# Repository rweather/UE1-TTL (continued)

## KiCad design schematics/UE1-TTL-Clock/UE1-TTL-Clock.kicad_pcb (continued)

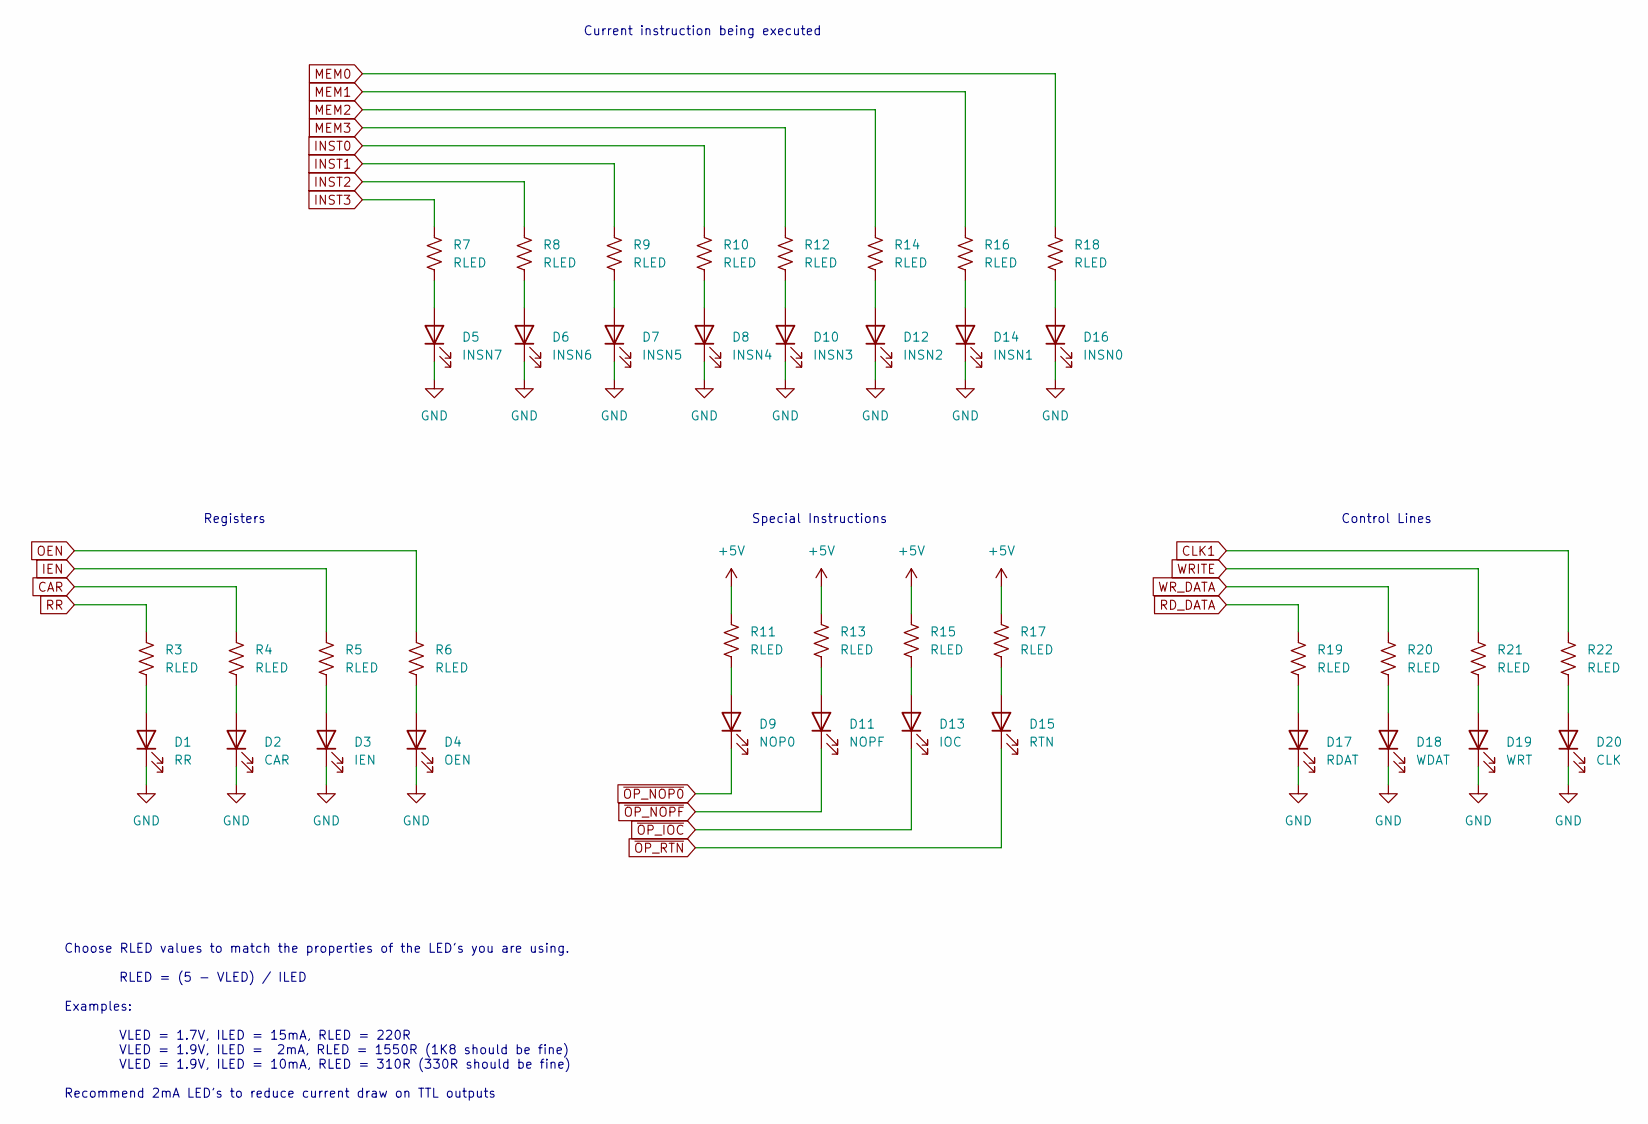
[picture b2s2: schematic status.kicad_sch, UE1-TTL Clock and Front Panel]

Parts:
D1: RR; LED_D3.0mm
D2: CAR; LED_D3.0mm
D3: IEN; LED_D3.0mm
D4: OEN; LED_D3.0mm
D5: INSN7; LED_D3.0mm
D6: INSN6; LED_D3.0mm
D7: INSN5; LED_D3.0mm
D8: INSN4; LED_D3.0mm
D9: NOP0; LED_D3.0mm
D10: INSN3; LED_D3.0mm
D11: NOPF; LED_D3.0mm
D12: INSN2; LED_D3.0mm
D13: IOC; LED_D3.0mm
D14: INSN1; LED_D3.0mm
D15: RTN; LED_D3.0mm
D16: INSN0; LED_D3.0mm
D17: RDAT; LED_D3.0mm
D18: WDAT; LED_D3.0mm
D19: WRT; LED_D3.0mm
D20: CLK; LED_D3.0mm
R3, R4, R5, R6, R7, R8, R9, R10, R11, R12, R13, R14, R15, R16, R17, R18, R19, R20, R21, R22: RLED; R_Axial_DIN0207_L6.3mm_D2.5mm_P7.62mm_Horizontal

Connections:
+5V: R11.1, R13.1, R15.1, R17.1; also elsewhere on the board
CAR: R4.1; also elsewhere on the board
CLK1: R22.1; also elsewhere on the board
GND: D1.1 (K), D2.1 (K), D3.1 (K), D4.1 (K), D5.1 (K), D6.1 (K), D7.1 (K), D8.1 (K), D10.1 (K), D12.1 (K), D14.1 (K), D16.1 (K), D17.1 (K), D18.1 (K), D19.1 (K), D20.1 (K); also elsewhere on the board
IEN: R5.1; also elsewhere on the board
INST0: R10.1; also elsewhere on the board
INST1: R9.1; also elsewhere on the board
INST2: R8.1; also elsewhere on the board
INST3: R7.1; also elsewhere on the board
MEM0: R18.1; also elsewhere on the board
MEM1: R16.1; also elsewhere on the board
MEM2: R14.1; also elsewhere on the board
MEM3: R12.1; also elsewhere on the board
unnamed: D1.2 (A), R3.2
unnamed: D2.2 (A), R4.2
unnamed: D3.2 (A), R5.2
unnamed: D4.2 (A), R6.2
unnamed: D5.2 (A), R7.2
unnamed: D6.2 (A), R8.2
unnamed: D7.2 (A), R9.2
unnamed: D8.2 (A), R10.2
unnamed: D9.2 (A), R11.2
unnamed: D10.2 (A), R12.2
unnamed: D11.2 (A), R13.2
unnamed: D12.2 (A), R14.2
unnamed: D13.2 (A), R15.2
unnamed: D14.2 (A), R16.2
unnamed: D15.2 (A), R17.2
unnamed: D16.2 (A), R18.2
unnamed: D17.2 (A), R19.2
unnamed: D18.2 (A), R20.2
unnamed: D19.2 (A), R21.2
unnamed: D20.2 (A), R22.2
OEN: R6.1; also elsewhere on the board
RD_DATA: R19.1; also elsewhere on the board
RR: R3.1; also elsewhere on the board
WRITE: R21.1; also elsewhere on the board
WR_DATA: R20.1; also elsewhere on the board
~OP_IOC: D13.1 (K); also elsewhere on the board
~OP_NOP0: D9.1 (K); also elsewhere on the board
~OP_NOPF: D11.1 (K); also elsewhere on the board
~OP_RTN: D15.1 (K); also elsewhere on the board

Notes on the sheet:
Choose RLED values to match the properties of the LED's you are using. RLED = (5 - VLED) / ILED Examples: VLED = 1.7V, ILED = 15mA, RLED = 220R VLED = 1.9V, ILED = 2mA, RLED = 1550R (1K8 should be fine) VLED = 1.9V, ILED = 10mA, RLED = 310R (330R should be fine) Recommend 2mA LED's to reduce curren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
Registers
Special Instructions
Control Lines
Current instruction being executed

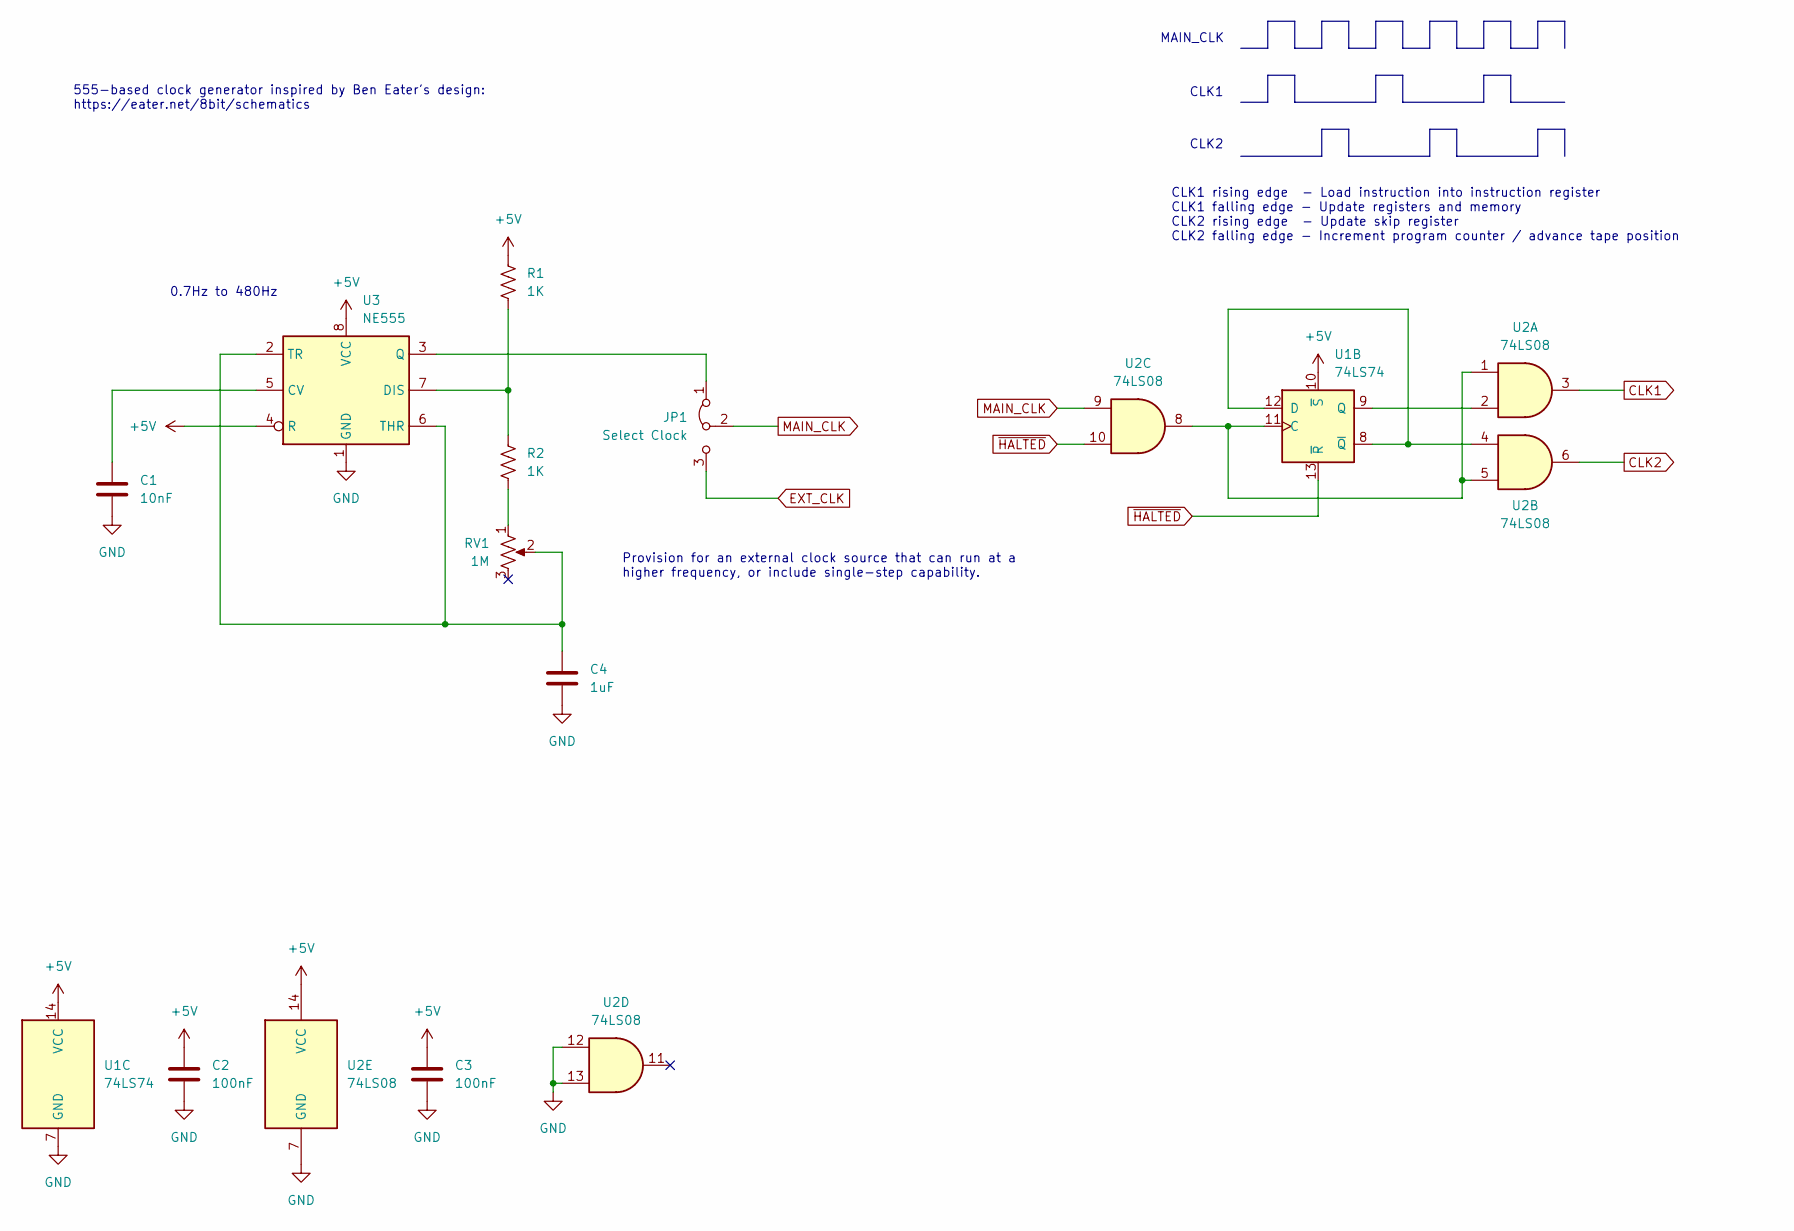
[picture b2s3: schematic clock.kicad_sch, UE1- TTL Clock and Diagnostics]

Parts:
C1: 10nF; C_Disc_D5.0mm_W2.5mm_P5.00mm
C2, C3: 100nF; C_Disc_D5.0mm_W2.5mm_P5.00mm
C4: 1uF; C_Disc_D5.0mm_W2.5mm_P5.00mm
JP1: Select Clock; PinHeader_1x03_P2.54mm_Vertical
R1, R2: 1K; R_Axial_DIN0207_L6.3mm_D2.5mm_P7.62mm_Horizontal
RV1: 1M; Potentiometer_Bourns_3266Y_Vertical
U1: 74LS74; DIP-14_W7.62mm
U2: 74LS08; DIP-14_W7.62mm
U3: NE555; DIP-8_W7.62mm

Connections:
+5V: C2.1, C3.1, R1.1, U1.10 (~S), U1.14 (VCC), U2.14 (VCC), U3.4 (R), U3.8 (VCC); also elsewhere on the board
CLK1: U2.3; also elsewhere on the board
CLK2: U2.6; also elsewhere on the board
EXT_CLK: JP1.3 (B); also elsewhere on the board
GND: C1.2, C2.2, C3.2, C4.2, U1.7 (GND), U2.7 (GND), U2.12, U2.13, U3.1 (GND); also elsewhere on the board
MAIN_CLK: JP1.2 (C), U2.9
unnamed 53: JP1.1 (A), U3.3 (Q); also elsewhere on the board
unnamed: R2.2, RV1.1
unnamed: U1.11 (C), U2.1, U2.5, U2.8
unnamed: U1.8 (~Q), U1.12 (D), U2.4
unnamed: U1.9 (Q), U2.2
unnamed: C1.1, U3.5 (CV)
unnamed: R1.2, R2.1, U3.7 (DIS)
unnamed: C4.1, RV1.2, U3.2 (TR), U3.6 (THR)
~HALTED: U1.13 (~R), U2.10; also elsewhere on the board

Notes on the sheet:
0.7Hz to 480Hz
Provision for an external clock source that can run at a higher frequency, or include single-step capability.
CLK1 rising edge - Load instruction into instruction register CLK1 falling edge - Update registers and memory CLK2 rising edge - Update skip register CLK2 falling edge - Increment program counter / advance tape position
555-based clock generator inspired by Ben Eater's design: https://eater.net/8bit/schematics
MAIN_CLK
CLK2
CLK1

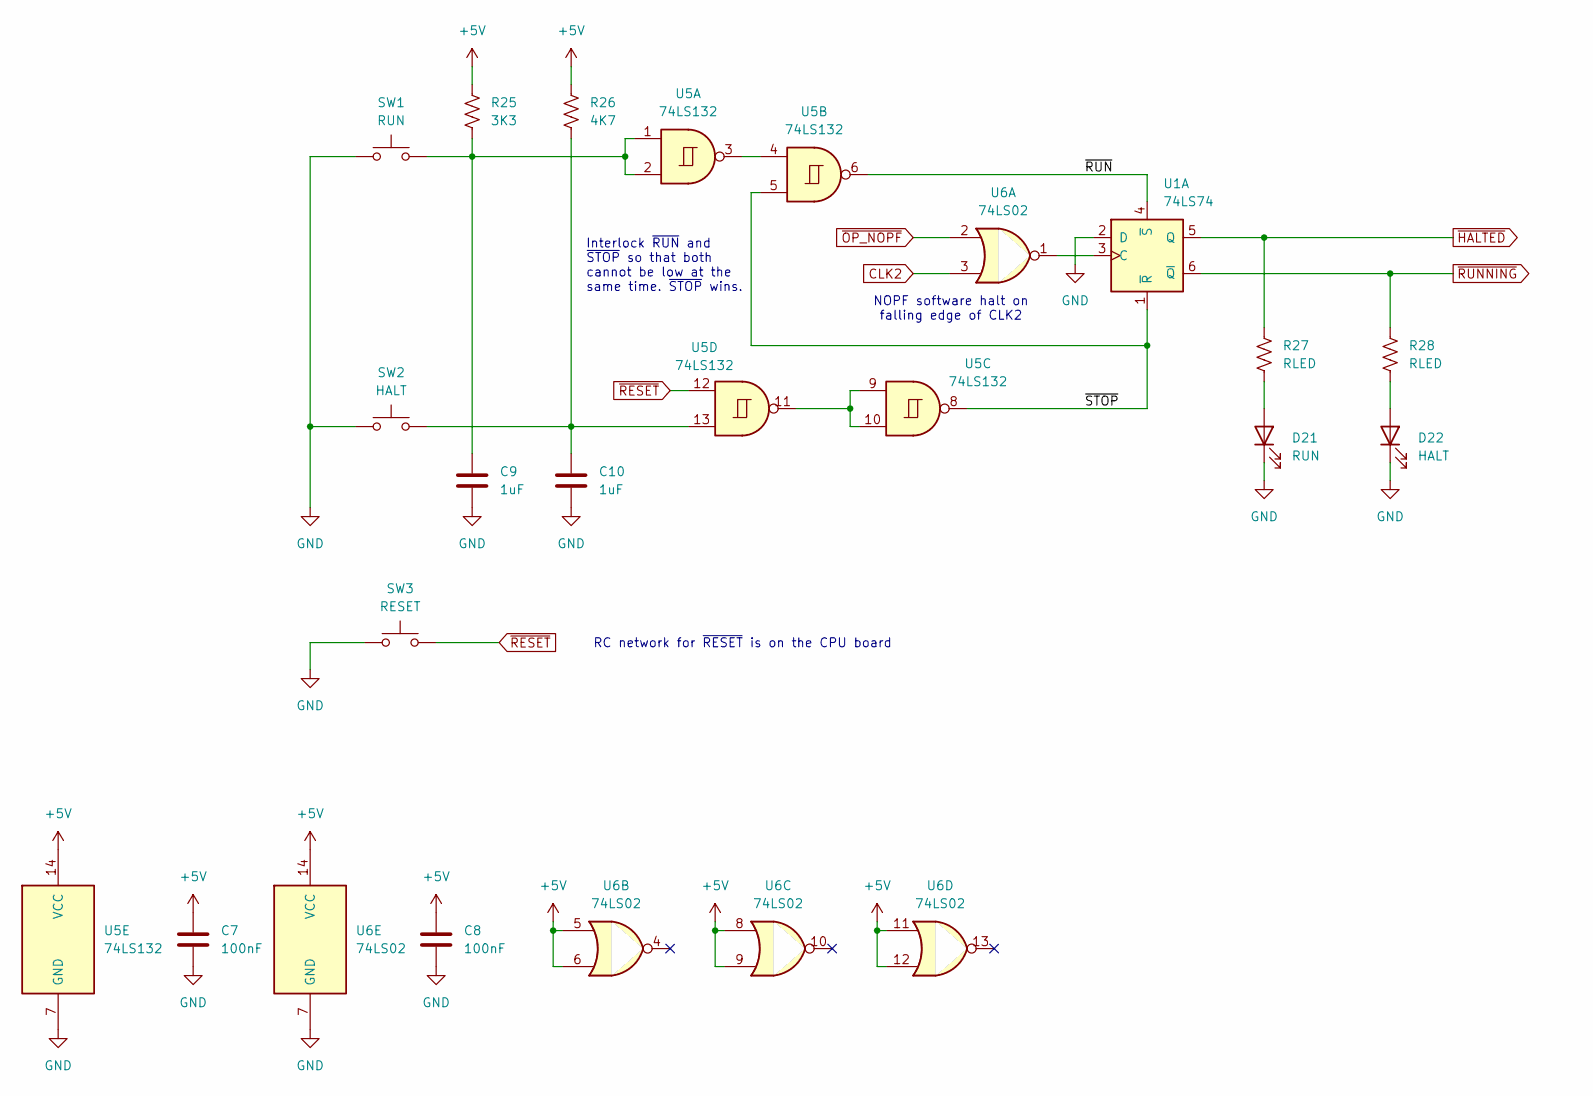
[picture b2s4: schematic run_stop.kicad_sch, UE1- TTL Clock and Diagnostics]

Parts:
C7, C8: 100nF; C_Disc_D5.0mm_W2.5mm_P5.00mm
C9, C10: 1uF; C_Disc_D5.0mm_W2.5mm_P5.00mm
D21: RUN; LED_D3.0mm
D22: HALT; LED_D3.0mm
R25: 3K3; R_Axial_DIN0207_L6.3mm_D2.5mm_P7.62mm_Horizontal
R26: 4K7; R_Axial_DIN0207_L6.3mm_D2.5mm_P7.62mm_Horizontal
R27, R28: RLED; R_Axial_DIN0207_L6.3mm_D2.5mm_P7.62mm_Horizontal
SW1: RUN; SW_PUSH_6mm
SW2: HALT; SW_PUSH_6mm
SW3: RESET; SW_PUSH_6mm
U1: 74LS74; DIP-14_W7.62mm
U5: 74LS132; DIP-14_W7.62mm
U6: 74LS02; DIP-14_W7.62mm

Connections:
+5V: C7.1, C8.1, R25.1, R26.1, U5.14 (VCC), U6.5, U6.6, U6.8, U6.9, U6.11, U6.12, U6.14 (VCC); also elsewhere on the board
/Run Stop/~RUN: U1.4 (~S), U5.6
/Run Stop/~STOP: U1.1 (~R), U5.5, U5.8
CLK2: U6.3; also elsewhere on the board
GND: C7.2, C8.2, C9.2, C10.2, D21.1 (K), D22.1 (K), SW1.1, SW2.1, SW3.1, U1.2 (D), U5.7 (GND), U6.7 (GND); also elsewhere on the board
unnamed: C9.1, R25.2, SW1.2, U5.1, U5.2
unnamed: C10.1, R26.2, SW2.2, U5.13
unnamed: D21.2 (A), R27.2
unnamed: D22.2 (A), R28.2
unnamed: U1.3 (C), U6.1
unnamed: U5.3, U5.4
unnamed: U5.9, U5.10, U5.11
~HALTED: R27.1, U1.5 (Q); also elsewhere on the board
~OP_NOPF: U6.2; also elsewhere on the board
~RESET: SW3.2, U5.12; also elsewhere on the board
~RUNNING: R28.1, U1.6 (~Q)

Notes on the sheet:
RC network for ~{RESET} is on the CPU board
NOPF software halt on falling edge of CLK2
Interlock ~{RUN} and ~{STOP} so that both cannot be low at the same time. ~{STOP} wins.

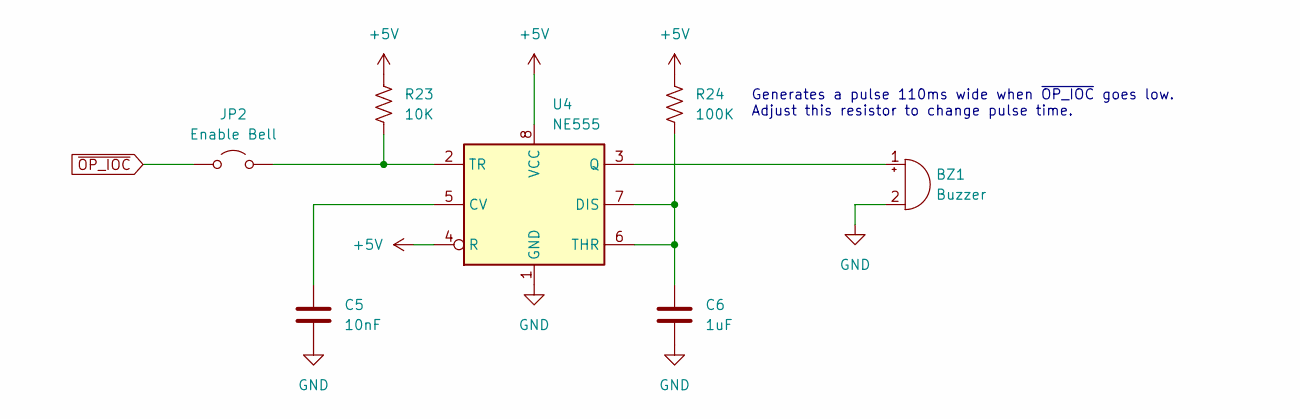
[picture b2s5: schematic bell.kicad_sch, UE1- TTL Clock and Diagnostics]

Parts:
BZ1: Buzzer; Buzzer_12x9.5RM7.6
C5: 10nF; C_Disc_D5.0mm_W2.5mm_P5.00mm
C6: 1uF; C_Disc_D5.0mm_W2.5mm_P5.00mm
JP2: Enable Bell; PinHeader_1x02_P2.54mm_Vertical
R23: 10K; R_Axial_DIN0207_L6.3mm_D2.5mm_P7.62mm_Horizontal
R24: 100K; R_Axial_DIN0207_L6.3mm_D2.5mm_P7.62mm_Horizontal
U4: NE555; DIP-8_W7.62mm

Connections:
+5V: R23.1, R24.1, U4.4 (R), U4.8 (VCC); also elsewhere on the board
GND: BZ1.2 (-), C5.2, C6.2, U4.1 (GND); also elsewhere on the board
unnamed: BZ1.1 (+), U4.3 (Q)
unnamed: JP2.2 (B), R23.2, U4.2 (TR)
unnamed: C5.1, U4.5 (CV)
unnamed: C6.1, R24.2, U4.6 (THR), U4.7 (DIS)
~OP_IOC: JP2.1 (A); also elsewhere on the board

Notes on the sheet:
Generates a pulse 110ms wide when ~{OP_IOC} goes low. Adjust this resistor to change pulse time.

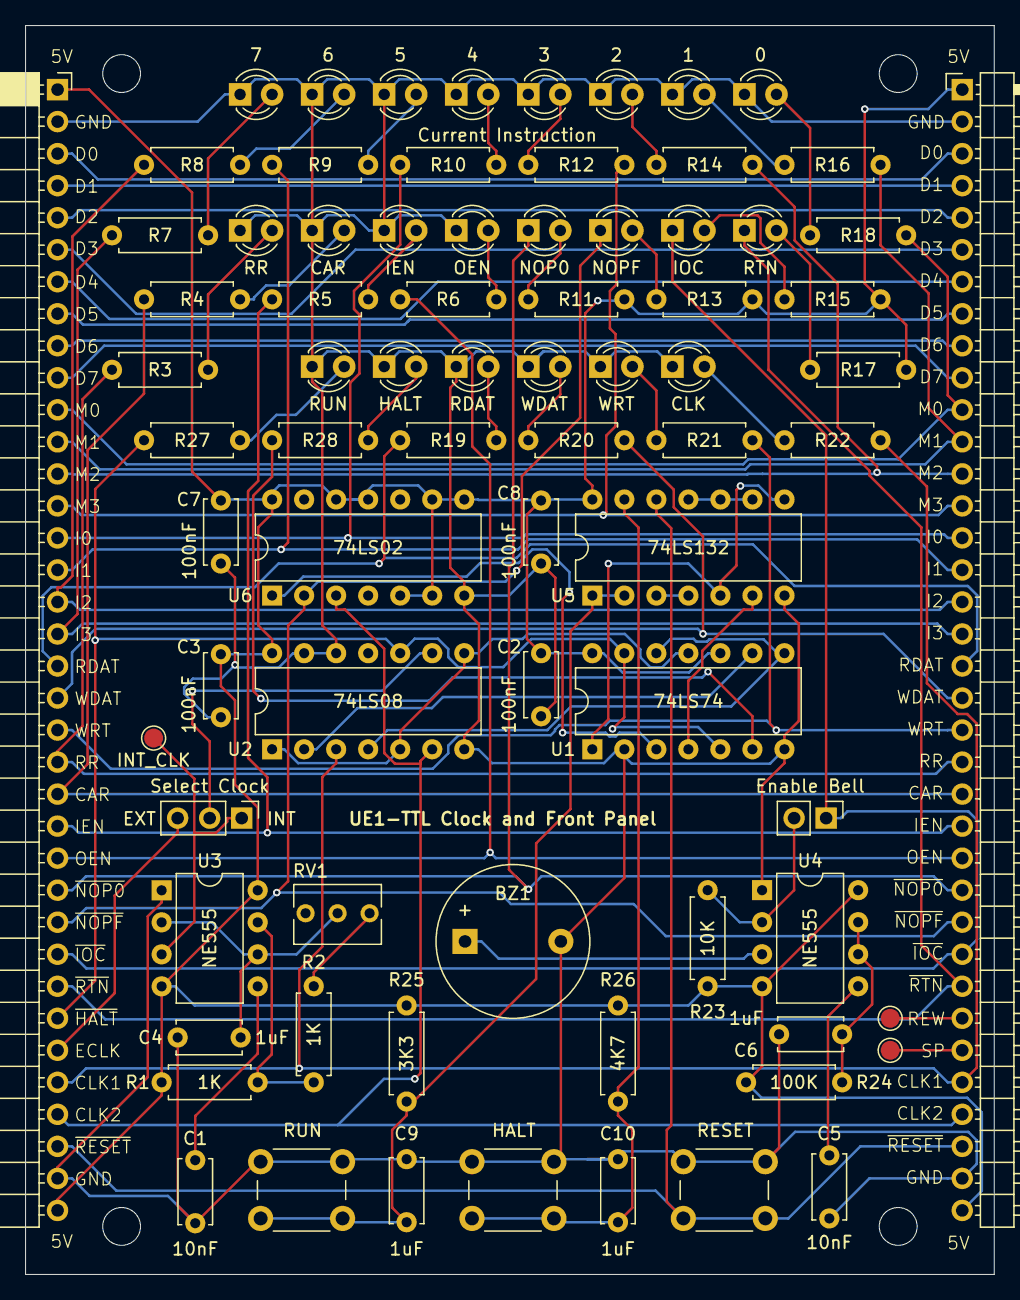
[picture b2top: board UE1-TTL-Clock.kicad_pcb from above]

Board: 2 copper layers, 76.8 x 99.1 mm, 82 parts (0 on the bottom side), 79 nets.

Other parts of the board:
TP1: REWIND; TestPoint_Pad_D1.5mm
TP2: SPARE; TestPoint_Pad_D1.5mm
TP3: INT_CLK; TestPoint_Pad_D1.5mm

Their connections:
unnamed 51: TP1.1; also elsewhere on the board
unnamed 52: TP2.1; also elsewhere on the board
unnamed 53: TP3.1; also elsewhere on the board

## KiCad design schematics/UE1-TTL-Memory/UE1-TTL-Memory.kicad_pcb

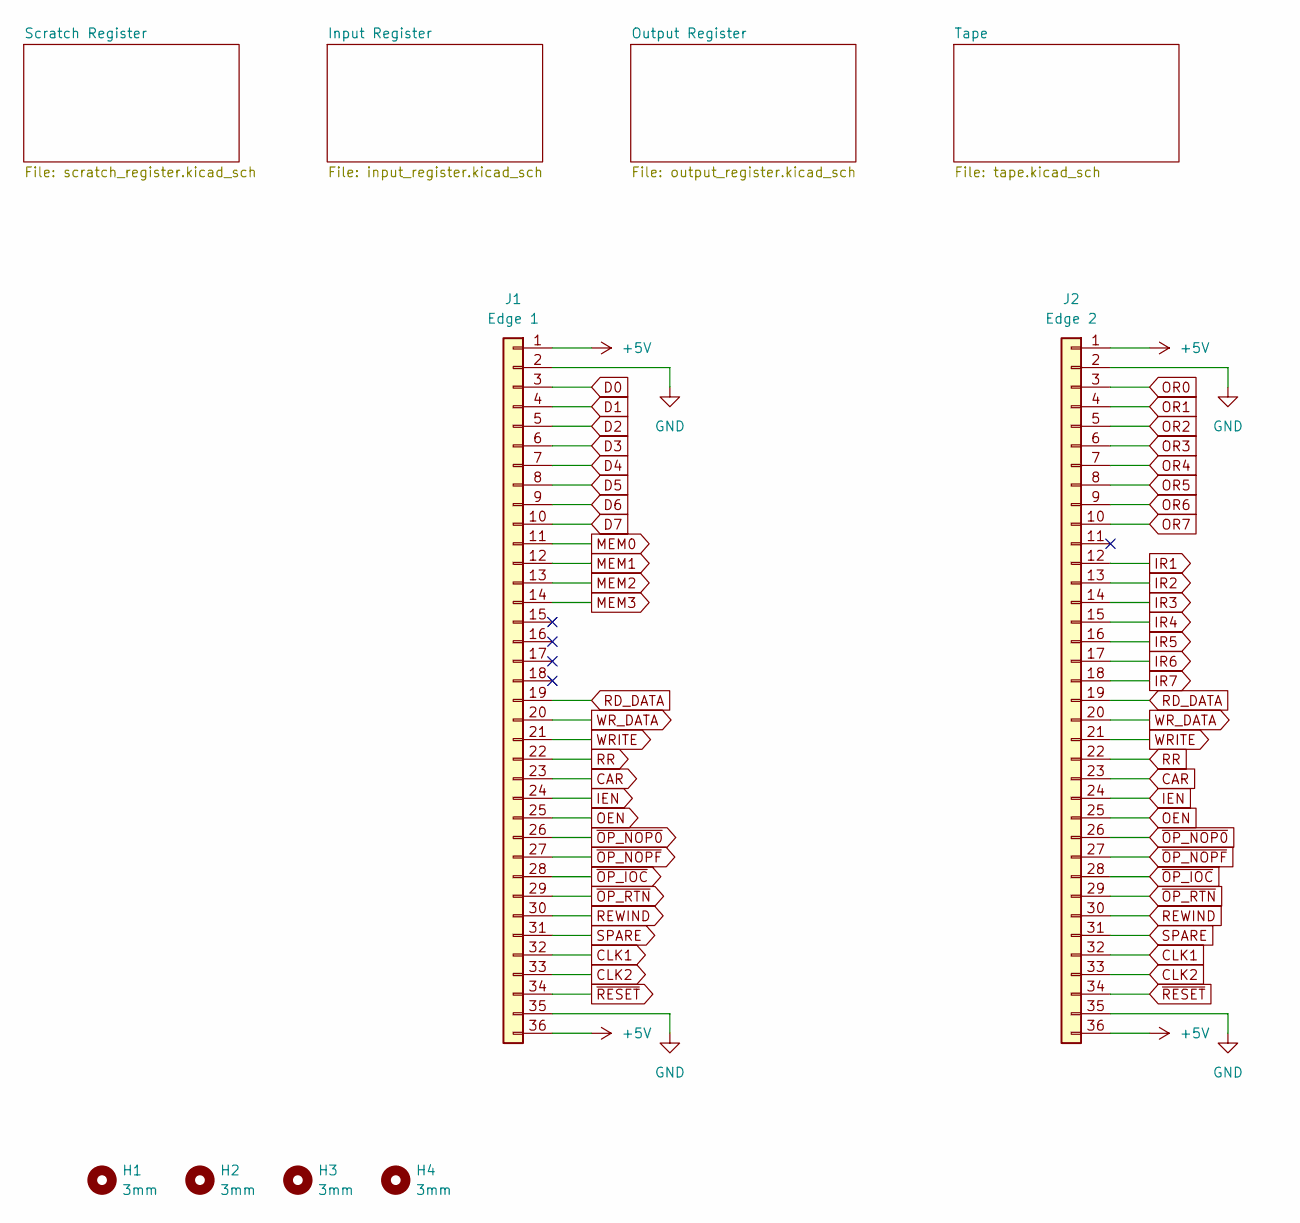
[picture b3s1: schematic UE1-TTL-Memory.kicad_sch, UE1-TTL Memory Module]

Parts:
H1, H2, H3, H4: 3mm; MountingHole_3mm
J1: Edge 1; PinSocket_1x36_P2.54mm_Horizontal
J2: Edge 2; PinHeader_1x36_P2.54mm_Horizontal

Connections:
+5V: J1.1, J1.36, J2.1, J2.36; also elsewhere on the board
CAR: J1.23, J2.23
CLK1: J1.32, J2.32
CLK2: J1.33, J2.33; also elsewhere on the board
D0: J1.3; also elsewhere on the board
D1: J1.4; also elsewhere on the board
D2: J1.5; also elsewhere on the board
D3: J1.6; also elsewhere on the board
D4: J1.7; also elsewhere on the board
D5: J1.8; also elsewhere on the board
D6: J1.9; also elsewhere on the board
D7: J1.10; also elsewhere on the board
GND: J1.2, J1.35, J2.2, J2.35; also elsewhere on the board
IEN: J1.24, J2.24
IR1: J2.12; also elsewhere on the board
IR2: J2.13; also elsewhere on the board
IR3: J2.14; also elsewhere on the board
IR4: J2.15; also elsewhere on the board
IR5: J2.16; also elsewhere on the board
IR6: J2.17; also elsewhere on the board
IR7: J2.18; also elsewhere on the board
MEM0: J1.11; also elsewhere on the board
MEM1: J1.12; also elsewhere on the board
MEM2: J1.13; also elsewhere on the board
MEM3: J1.14; also elsewhere on the board
OEN: J1.25, J2.25
OR0: J2.3; also elsewhere on the board
OR1: J2.4; also elsewhere on the board
OR2: J2.5; also elsewhere on the board
OR3: J2.6; also elsewhere on the board
OR4: J2.7; also elsewhere on the board
OR5: J2.8; also elsewhere on the board
OR6: J2.9; also elsewhere on the board
OR7: J2.10; also elsewhere on the board
RD_DATA: J1.19, J2.19; also elsewhere on the board
REWIND: J1.30, J2.30; also elsewhere on the board
RR: J1.22, J2.22; also elsewhere on the board
SPARE: J1.31, J2.31
WRITE: J1.21, J2.21; also elsewhere on the board
WR_DATA: J1.20, J2.20; also elsewhere on the board
~OP_IOC: J1.28, J2.28
~OP_NOP0: J1.26, J2.26
~OP_NOPF: J1.27, J2.27
~OP_RTN: J1.29, J2.29
~RESET: J1.34, J2.34; also elsewhere on the board

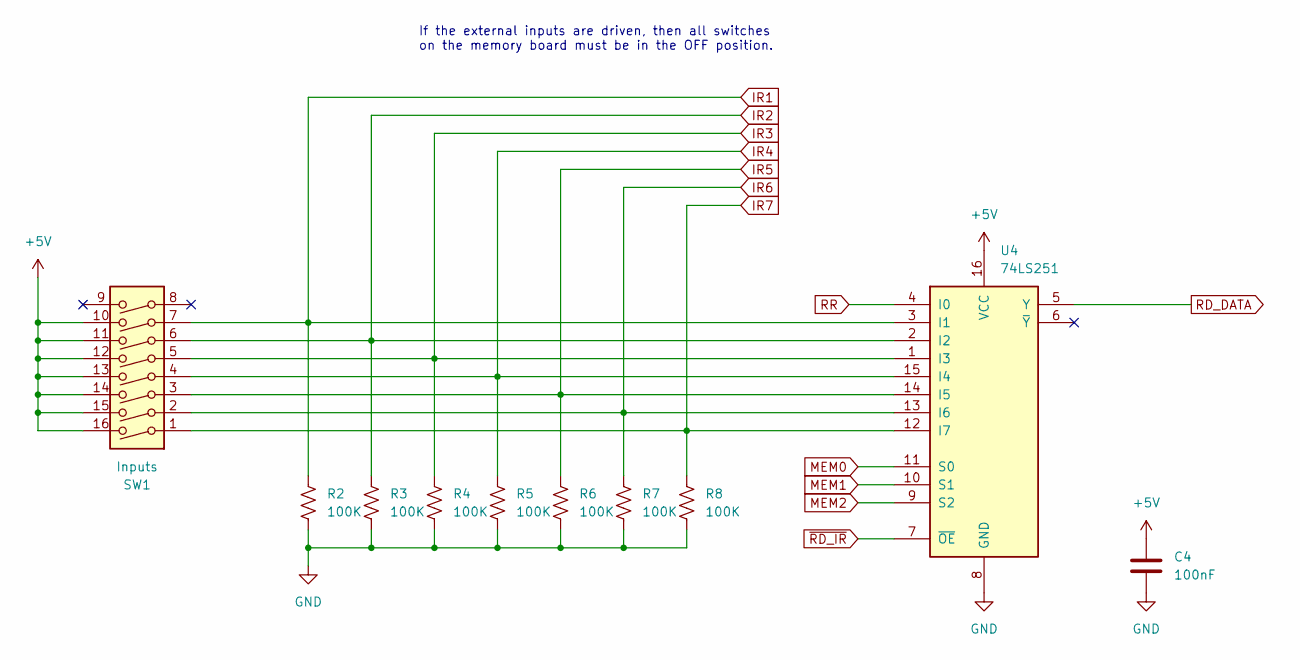
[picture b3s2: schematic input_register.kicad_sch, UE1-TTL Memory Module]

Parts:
C4: 100nF; C_Disc_D5.0mm_W2.5mm_P5.00mm
R2, R3, R4, R5, R6, R7, R8: 100K; R_Axial_DIN0207_L6.3mm_D2.5mm_P7.62mm_Horizontal
SW1: Inputs; SW_DIP_SPSTx08_Slide_6.7x21.88mm_W7.62mm_P2.54mm_LowProfile
U4: 74LS251; DIP-16_W7.62mm

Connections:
+5V: C4.1, SW1.10, SW1.11, SW1.12, SW1.13, SW1.14, SW1.15, SW1.16, U4.16 (VCC); also elsewhere on the board
GND: C4.2, R2.2, R3.2, R4.2, R5.2, R6.2, R7.2, R8.2, U4.8 (GND); also elsewhere on the board
IR1: R2.1, SW1.7, U4.3 (I1); also elsewhere on the board
IR2: R3.1, SW1.6, U4.2 (I2); also elsewhere on the board
IR3: R4.1, SW1.5, U4.1 (I3); also elsewhere on the board
IR4: R5.1, SW1.4, U4.15 (I4); also elsewhere on the board
IR5: R6.1, SW1.3, U4.14 (I5); also elsewhere on the board
IR6: R7.1, SW1.2, U4.13 (I6); also elsewhere on the board
IR7: R8.1, SW1.1, U4.12 (I7); also elsewhere on the board
MEM0: U4.11 (S0); also elsewhere on the board
MEM1: U4.10 (S1); also elsewhere on the board
MEM2: U4.9 (S2); also elsewhere on the board
RD_DATA: U4.5 (Y); also elsewhere on the board
RR: U4.4 (I0); also elsewhere on the board
~RD_IR: U4.7 (~OE); also elsewhere on the board

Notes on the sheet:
If the external inputs are driven, then all switches on the memory board must be in the OFF position.

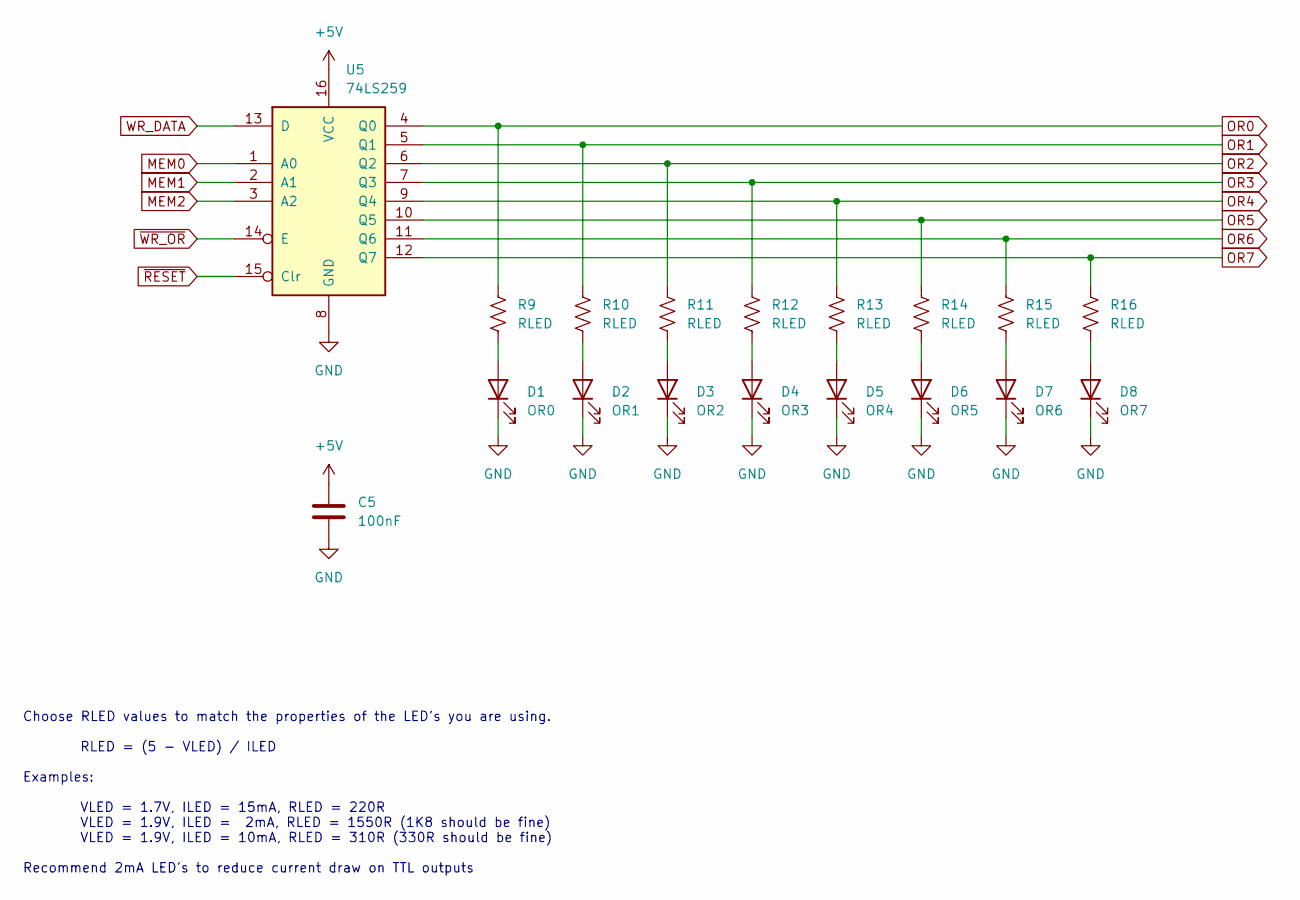
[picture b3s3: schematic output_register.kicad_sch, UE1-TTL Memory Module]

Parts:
C5: 100nF; C_Disc_D5.0mm_W2.5mm_P5.00mm
D1: OR0; LED_D3.0mm
D2: OR1; LED_D3.0mm
D3: OR2; LED_D3.0mm
D4: OR3; LED_D3.0mm
D5: OR4; LED_D3.0mm
D6: OR5; LED_D3.0mm
D7: OR6; LED_D3.0mm
D8: OR7; LED_D3.0mm
R9, R10, R11, R12, R13, R14, R15, R16: RLED; R_Axial_DIN0207_L6.3mm_D2.5mm_P7.62mm_Horizontal
U5: 74LS259; DIP-16_W7.62mm

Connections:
+5V: C5.1, U5.16 (VCC); also elsewhere on the board
GND: C5.2, D1.1 (K), D2.1 (K), D3.1 (K), D4.1 (K), D5.1 (K), D6.1 (K), D7.1 (K), D8.1 (K), U5.8 (GND); also elsewhere on the board
MEM0: U5.1 (A0); also elsewhere on the board
MEM1: U5.2 (A1); also elsewhere on the board
MEM2: U5.3 (A2); also elsewhere on the board
unnamed: D1.2 (A), R9.2
unnamed: D2.2 (A), R10.2
unnamed: D3.2 (A), R11.2
unnamed: D4.2 (A), R12.2
unnamed: D5.2 (A), R13.2
unnamed: D6.2 (A), R14.2
unnamed: D7.2 (A), R15.2
unnamed: D8.2 (A), R16.2
OR0: R9.1, U5.4 (Q0); also elsewhere on the board
OR1: R10.1, U5.5 (Q1); also elsewhere on the board
OR2: R11.1, U5.6 (Q2); also elsewhere on the board
OR3: R12.1, U5.7 (Q3); also elsewhere on the board
OR4: R13.1, U5.9 (Q4); also elsewhere on the board
OR5: R14.1, U5.10 (Q5); also elsewhere on the board
OR6: R15.1, U5.11 (Q6); also elsewhere on the board
OR7: R16.1, U5.12 (Q7); also elsewhere on the board
WR_DATA: U5.13 (D); also elsewhere on the board
~RESET: U5.15 (Clr); also elsewhere on the board
~WR_OR: U5.14 (E); also elsewhere on the board

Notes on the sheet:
Choose RLED values to match the properties of the LED's you are using. RLED = (5 - VLED) / ILED Examples: VLED = 1.7V, ILED = 15mA, RLED = 220R VLED = 1.9V, ILED = 2mA, RLED = 1550R (1K8 should be fine) VLED = 1.9V, ILED = 10mA, RLED = 310R (330R should be fine) Recommend 2mA LED's to reduce curren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

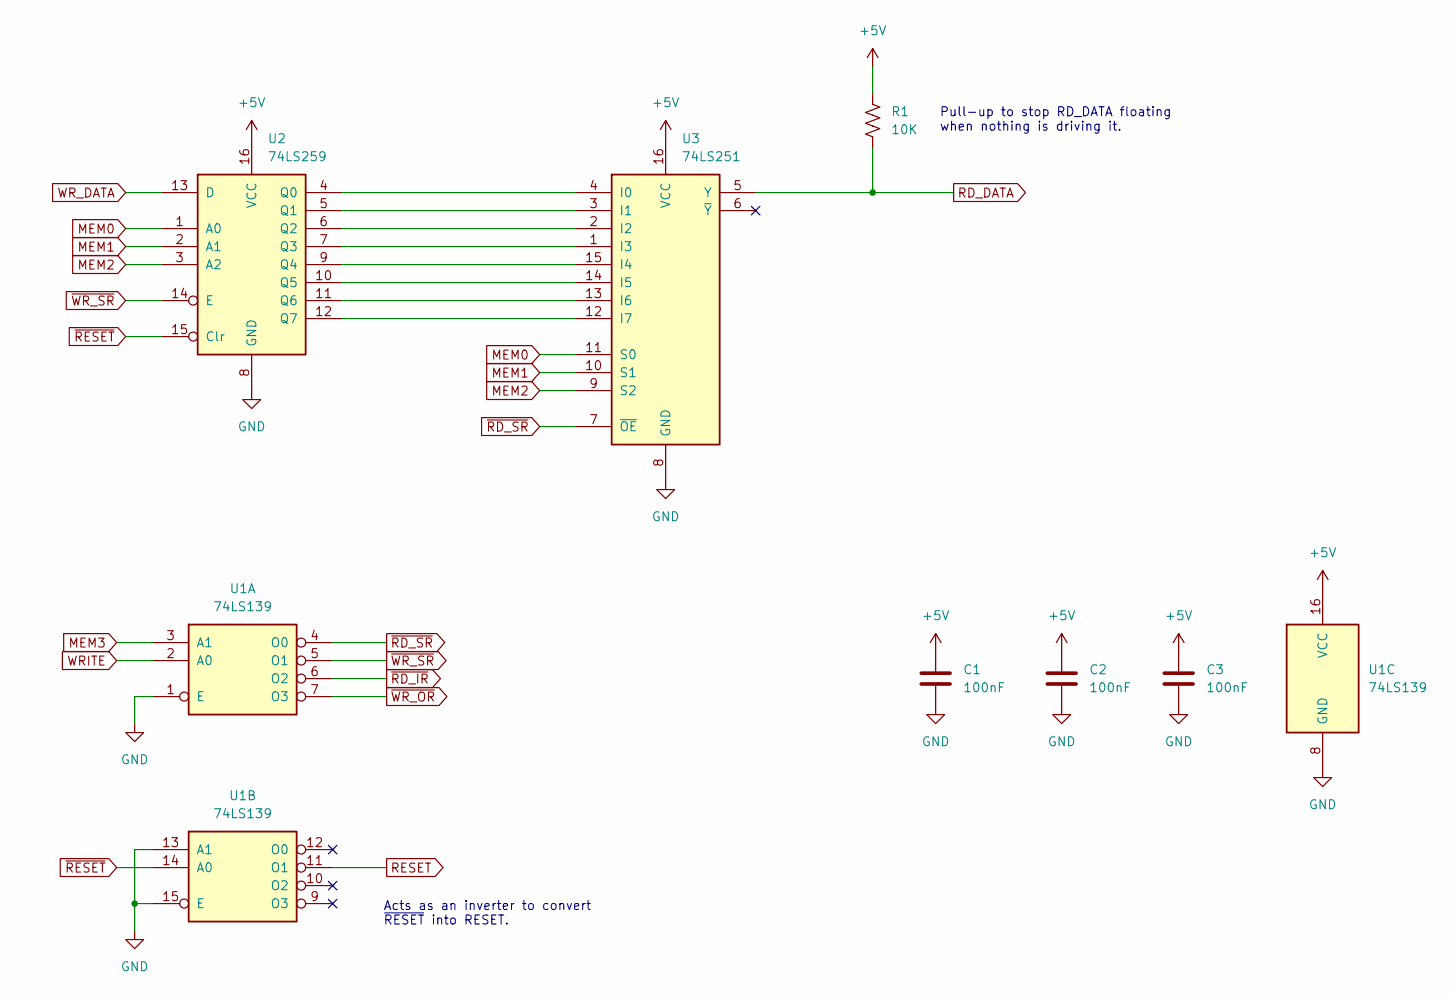
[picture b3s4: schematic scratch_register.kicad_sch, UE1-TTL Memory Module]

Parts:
C1, C2, C3: 100nF; C_Disc_D5.0mm_W2.5mm_P5.00mm
R1: 10K; R_Axial_DIN0207_L6.3mm_D2.5mm_P7.62mm_Horizontal
U1: 74LS139; DIP-16_W7.62mm
U2: 74LS259; DIP-16_W7.62mm
U3: 74LS251; DIP-16_W7.62mm

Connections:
+5V: C1.1, C2.1, C3.1, R1.1, U1.16 (VCC), U2.16 (VCC), U3.16 (VCC); also elsewhere on the board
GND: C1.2, C2.2, C3.2, U1.1 (E), U1.8 (GND), U1.13 (A1), U1.15 (E), U2.8 (GND), U3.8 (GND); also elsewhere on the board
MEM0: U2.1 (A0), U3.11 (S0); also elsewhere on the board
MEM1: U2.2 (A1), U3.10 (S1); also elsewhere on the board
MEM2: U2.3 (A2), U3.9 (S2); also elsewhere on the board
MEM3: U1.3 (A1); also elsewhere on the board
unnamed: U2.4 (Q0), U3.4 (I0)
unnamed: U2.5 (Q1), U3.3 (I1)
unnamed: U2.6 (Q2), U3.2 (I2)
unnamed: U2.7 (Q3), U3.1 (I3)
unnamed: U2.9 (Q4), U3.15 (I4)
unnamed: U2.10 (Q5), U3.14 (I5)
unnamed: U2.11 (Q6), U3.13 (I6)
unnamed: U2.12 (Q7), U3.12 (I7)
RD_DATA: R1.2, U3.5 (Y); also elsewhere on the board
RESET: U1.11 (O1); also elsewhere on the board
WRITE: U1.2 (A0); also elsewhere on the board
WR_DATA: U2.13 (D); also elsewhere on the board
~RD_IR: U1.6 (O2); also elsewhere on the board
~RD_SR: U1.4 (O0), U3.7 (~OE)
~RESET: U1.14 (A0), U2.15 (Clr); also elsewhere on the board
~WR_OR: U1.7 (O3); also elsewhere on the board
~WR_SR: U1.5 (O1), U2.14 (E)

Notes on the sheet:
Acts as an inverter to convert ~{RESET} into RESET.
Pull-up to stop RD_DATA floating when nothing is driving it.
